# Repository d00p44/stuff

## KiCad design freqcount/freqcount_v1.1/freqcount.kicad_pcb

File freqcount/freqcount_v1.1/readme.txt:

v1.0
  -Cs am Quarz falsch angebunden 
  -kein ISP-Stecker
v1.1
  -Cs am Quarz angepasst
  -ISP-Stecker ergänzt

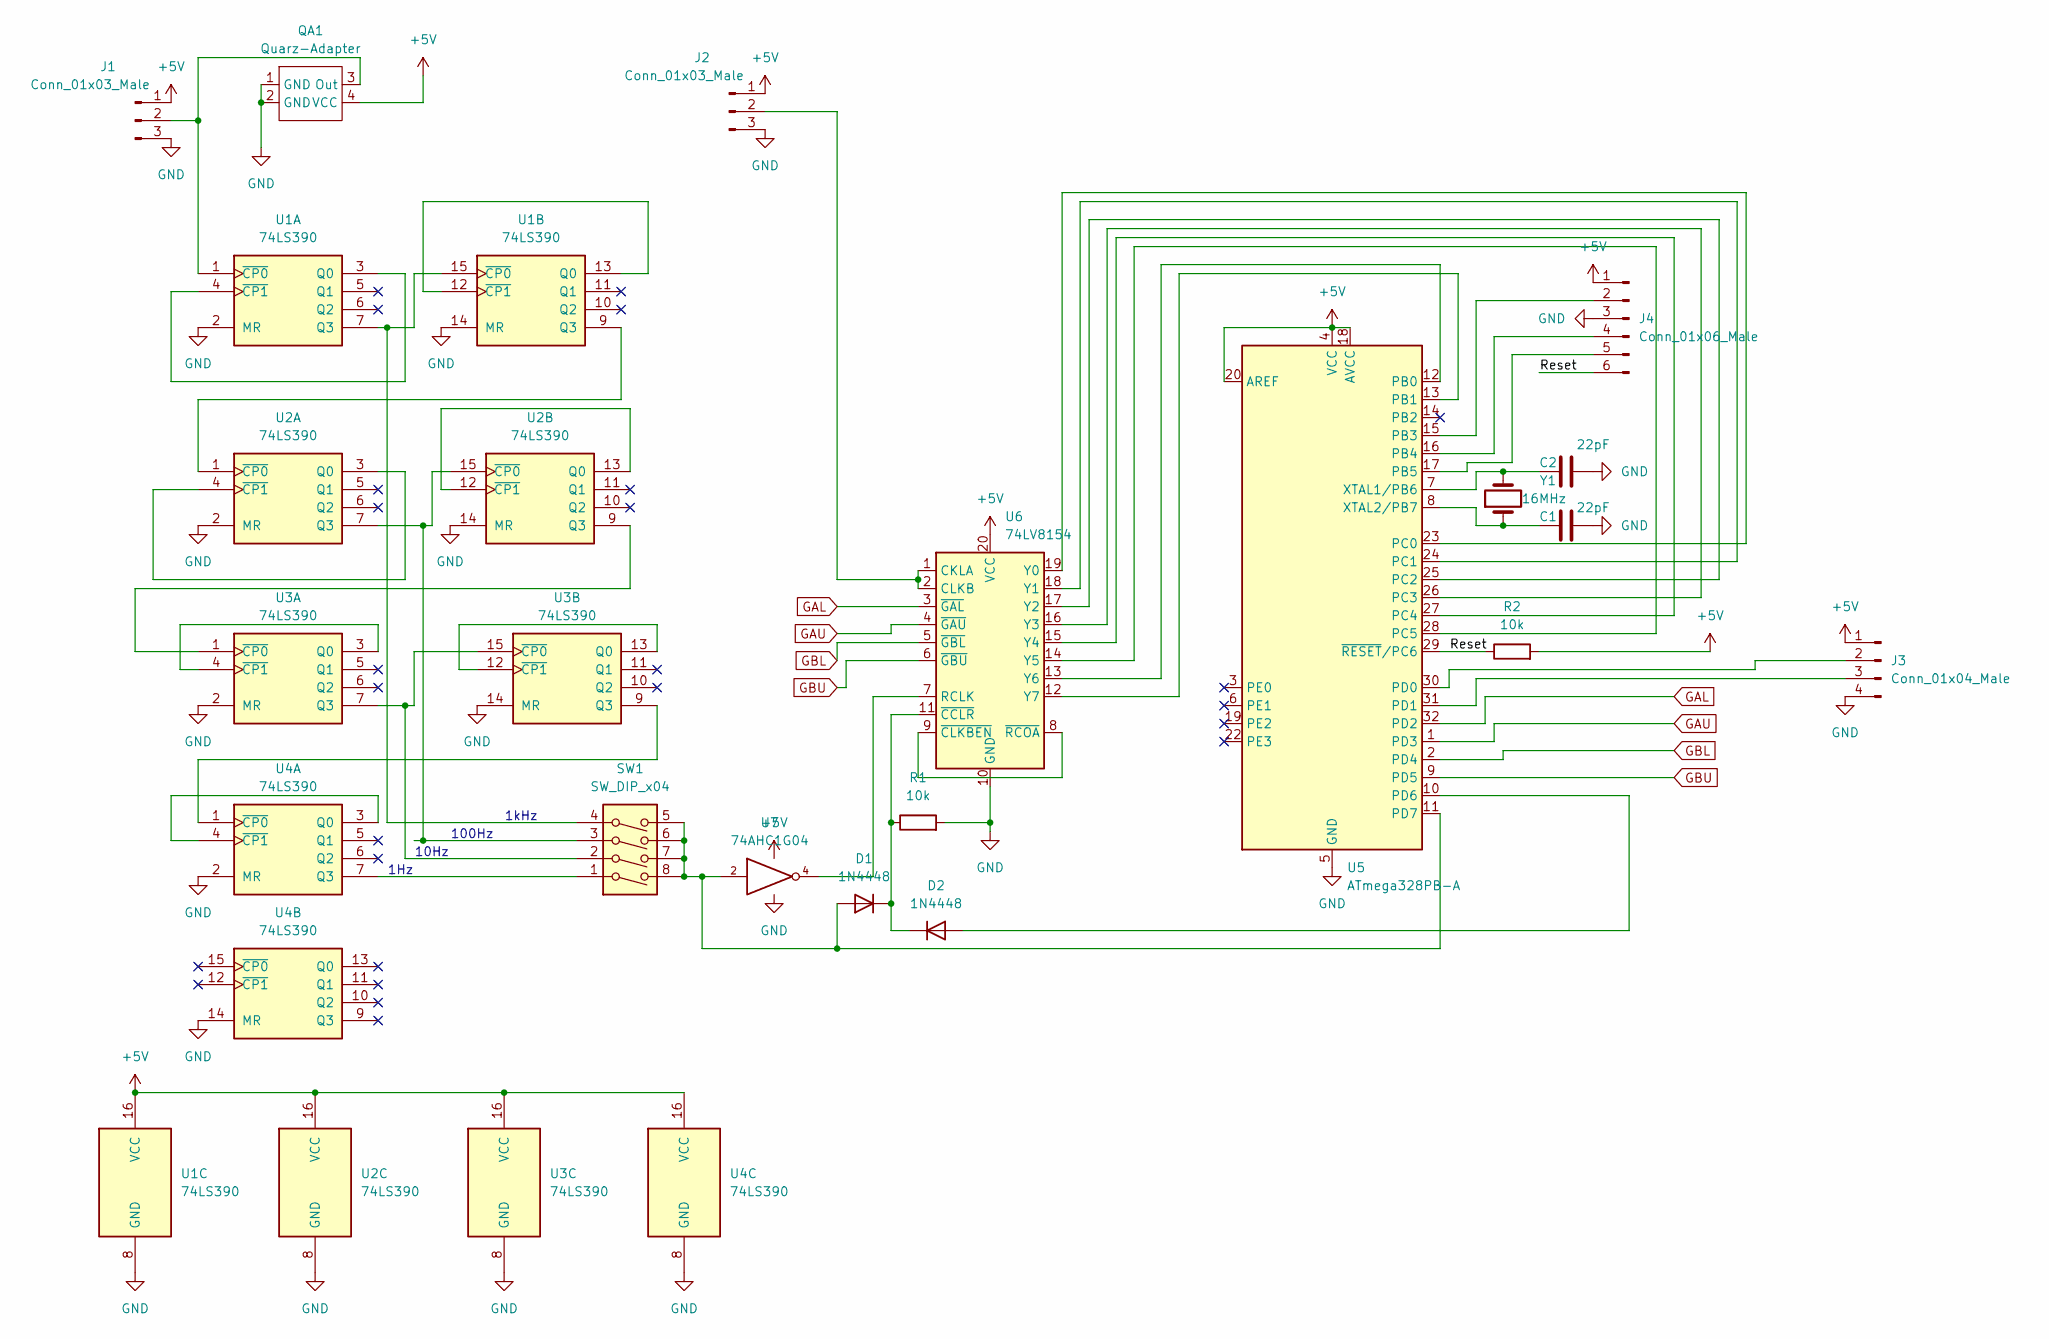
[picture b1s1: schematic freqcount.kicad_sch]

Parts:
C1, C2: 22pF; C_0603_1608Metric
D1, D2: 1N4448; D_SOD-323
J1, J2: Conn_01x03_Male; JST_PH_B3B-PH-K_1x03_P2.00mm_Vertical
J3: Conn_01x04_Male; JST_EH_B4B-EH-A_1x04_P2.50mm_Vertical
J4: Conn_01x06_Male; Molex_PicoBlade_53047-0610_1x06_P1.25mm_Vertical
QA1: Quarz-Adapter
R1, R2: 10k; R_0603_1608Metric
SW1: SW_DIP_x04; SW_DIP_SPSTx04_Slide_KingTek_DSHP04TS_W7.62mm_P1.27mm
U1, U2, U3, U4: 74LS390; SSOP-16_4.4x5.2mm_P0.65mm
U5: ATmega328PB-A; TQFP-32_7x7mm_P0.8mm
U6: 74LV8154; TSSOP-20_4.4x6.5mm_P0.65mm
U7: 74AHC1G04; SOT-23-5
Y1: 16MHz; Crystal_SMD_EuroQuartz_MJ-4Pin_5.0x3.2mm

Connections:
+5V: J1.1, J2.1, J3.1, J4.1, QA1.4 (VCC), R2.2, U1.16 (VCC), U2.16 (VCC), U3.16 (VCC), U4.16 (VCC), U5.4 (VCC), U5.18 (AVCC), U5.20 (AREF), U6.20 (VCC), U7.5 (VCC)
/Reset: J4.6, R2.1, U5.29 (~RESET/PC6)
GAL: U5.32 (PD2), U6.3 (~GAL)
GAU: U5.1 (PD3), U6.4 (~GAU)
GBL: U5.2 (PD4), U6.5 (~GBL)
GBU: U5.9 (PD5), U6.6 (~GBU)
GND: C1.2, C2.2, J1.3, J2.3, J3.4, J4.3, QA1.1 (GND), QA1.2 (GND), R1.2, U1.2 (MR), U1.8 (GND), U1.14 (MR), U2.2 (MR), U2.8 (GND), U2.14 (MR), U3.2 (MR), U3.8 (GND), U3.14 (MR), U4.2 (MR), U4.8 (GND), U4.14 (MR), U5.5 (GND), U5.21 (GND), U6.10 (GND), U7.3 (GND)
unnamed: D1.1 (K), D2.1 (K), R1.1, U6.11 (~CCLR)
unnamed: D1.2 (A), SW1.5, SW1.6, SW1.7, SW1.8, U5.11 (PD7), U7.2
unnamed: D2.2 (A), U5.10 (PD6)
unnamed: J1.2, QA1.3 (Out), U1.1 (~CP0)
unnamed: J2.2, U6.1 (CKLA), U6.2 (CLKB)
unnamed: SW1.1, U4.7 (Q3)
unnamed: SW1.2, U3.7 (Q3), U3.15 (~CP0)
unnamed: SW1.3, U2.7 (Q3), U2.15 (~CP0)
unnamed: SW1.4, U1.7 (Q3), U1.15 (~CP0)
unnamed: U1.3 (Q0), U1.4 (~CP1)
unnamed: U1.9 (Q3), U2.1 (~CP0)
unnamed: U1.12 (~CP1), U1.13 (Q0)
unnamed: U2.3 (Q0), U2.4 (~CP1)
unnamed: U2.9 (Q3), U3.1 (~CP0)
unnamed: U2.12 (~CP1), U2.13 (Q0)
unnamed: U3.3 (Q0), U3.4 (~CP1)
unnamed: U3.9 (Q3), U4.1 (~CP0)
unnamed: U3.12 (~CP1), U3.13 (Q0)
unnamed: U4.3 (Q0), U4.4 (~CP1)
unnamed: C2.1, U5.7 (XTAL1/PB6), Y1.2
unnamed: C1.1, U5.8 (XTAL2/PB7), Y1.1
unnamed: U5.12 (PB0), U6.13 (Y6)
unnamed: U5.13 (PB1), U6.12 (Y7)
unnamed: J4.2, U5.15 (PB3)
unnamed: J4.4, U5.16 (PB4)
unnamed: J4.5, U5.17 (PB5)
unnamed: U5.23 (PC0), U6.19 (Y0)
unnamed: U5.24 (PC1), U6.18 (Y1)
unnamed: U5.25 (PC2), U6.17 (Y2)
unnamed: U5.26 (PC3), U6.16 (Y3)
unnamed: U5.27 (PC4), U6.15 (Y4)
unnamed: U5.28 (PC5), U6.14 (Y5)
unnamed: J3.2, U5.30 (PD0)
unnamed: J3.3, U5.31 (PD1)
unnamed: U6.7 (RCLK), U7.4
unnamed: U6.8 (~RCOA), U6.9 (~CLKBEN)

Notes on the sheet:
1kHz
100Hz
1Hz
10Hz

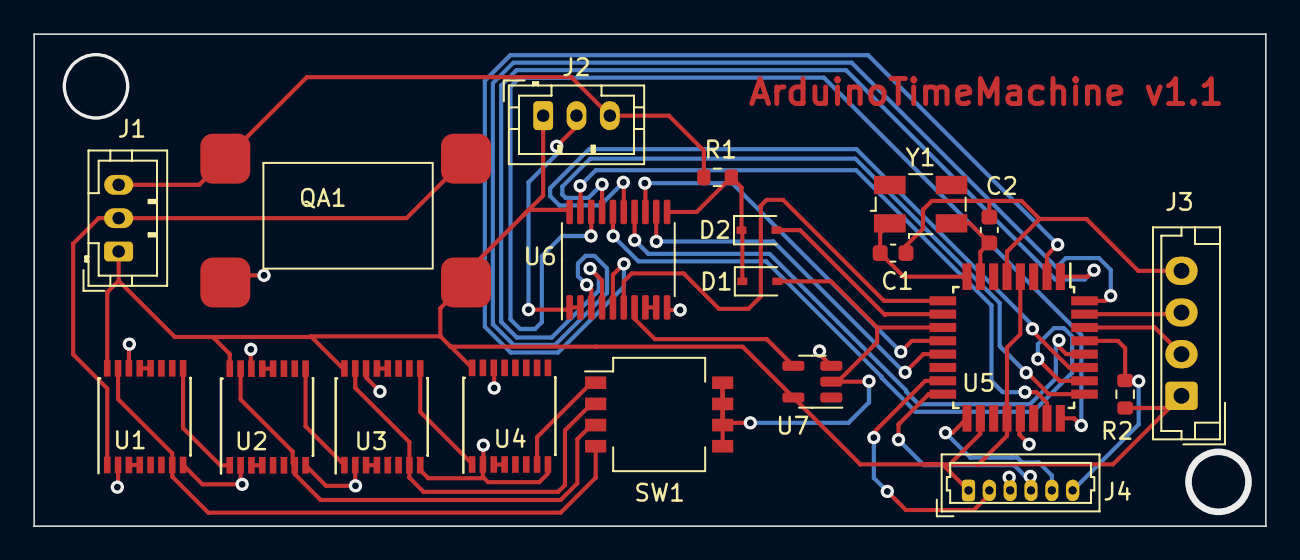
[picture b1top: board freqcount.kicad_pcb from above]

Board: 2 copper layers, 73.9 x 29.5 mm, 20 parts (0 on the bottom side), 43 nets.

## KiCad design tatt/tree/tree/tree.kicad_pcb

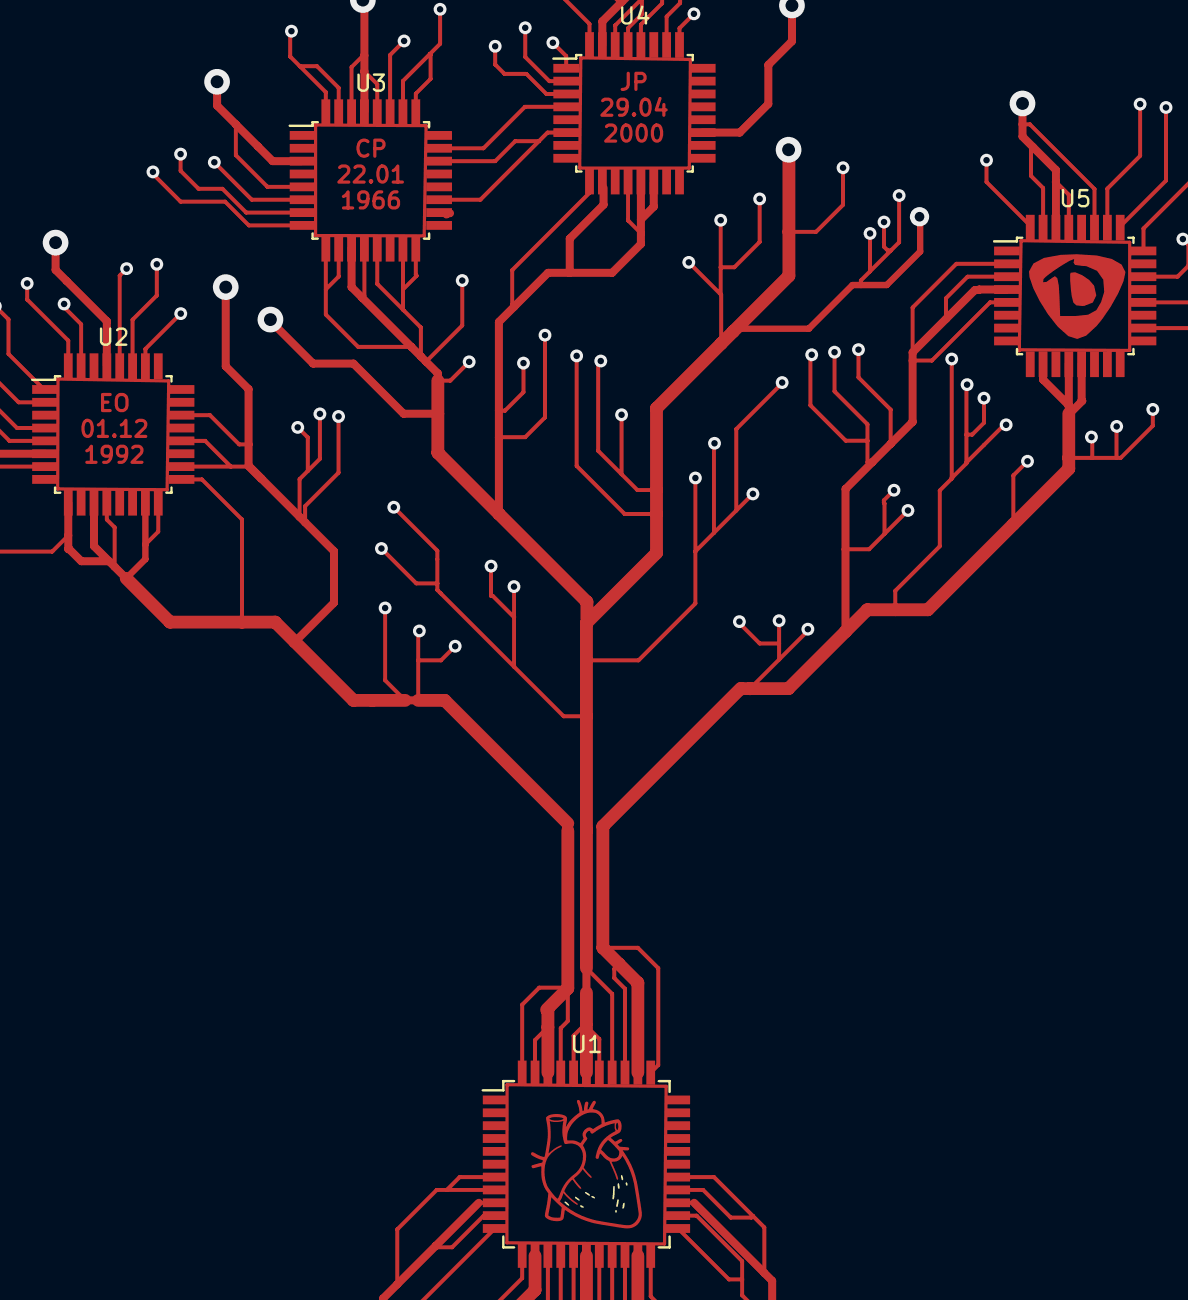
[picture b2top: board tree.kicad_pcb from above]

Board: 2 copper layers, 5 parts (0 on the bottom side), 8 nets.

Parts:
U1: ATmega16L-8A; TQFP-44_10x10mm_P0.8mm
U2, U3, U4, U5: ATmega8-16A; TQFP-32_7x7mm_P0.8mm

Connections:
unnamed: U1.5 (VCC), U5.27 (PC4), U5.29 (PC6/~RESET), U5.30 (PD0), U5.31 (PD1)
unnamed: U1.6 (GND), U1.16 (PD7), U1.17 (VCC), U1.18 (GND), U1.28 (GND)
unnamed: U2.3 (GND), U2.5 (GND)
unnamed: U1.34 (PA3), U1.35 (PA2), U1.36 (PA1), U2.4 (VCC), U2.6 (VCC), U5.2 (PD4), U5.3 (GND), U5.4 (VCC), U5.5 (GND), U5.7 (PB6/XTAL1), U5.10 (PD6), U5.12 (PB0), U5.13 (PB1)
unnamed: U3.3 (GND), U3.5 (GND)
unnamed: U3.4 (VCC), U3.6 (VCC)
unnamed: U4.3 (GND), U4.5 (GND)
unnamed: U4.4 (VCC), U4.6 (VCC)

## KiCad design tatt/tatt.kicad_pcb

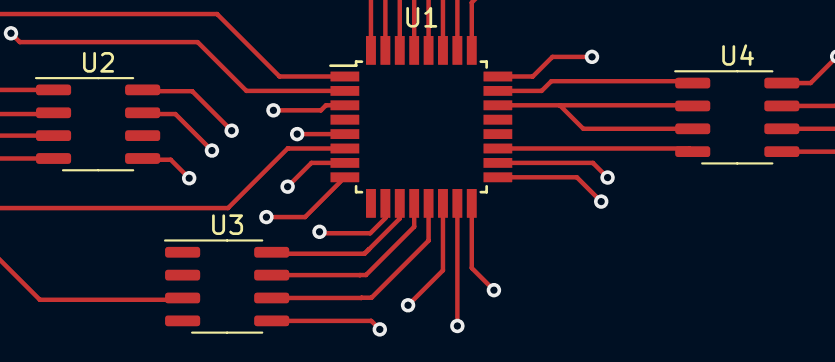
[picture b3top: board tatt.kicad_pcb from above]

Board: 2 copper layers, 4 parts (0 on the bottom side), 13 nets.

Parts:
U1: ATmega8-16A; TQFP-32_7x7mm_P0.8mm
U2, U3, U4: HV9930LG-G; SOIC-8_3.9x4.9mm_P1.27mm

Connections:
GND: U1.3 (GND), U1.5 (GND), U1.20 (AREF), U1.21 (AGND), U1.22 (ADC7), U2.3 (GND), U3.3 (GND), U4.2 (CS1), U4.3 (GND)
unnamed: U1.1 (PD3), U2.1 (VIN)
unnamed: U1.2 (PD4), U2.2 (CS1)
unnamed: U1.7 (PB6/XTAL1), U2.5 (PWMD)
unnamed: U1.8 (PB7/XTAL2), U2.7 (CS2)
unnamed: U1.9 (PD5), U2.8 (REF)
unnamed: U1.10 (PD6), U3.5 (PWMD)
unnamed: U1.4 (VCC), U1.6 (VCC), U1.18 (AVCC), U2.4 (GATE)
unnamed: U1.23 (PC0), U4.1 (VIN)
unnamed: U1.13 (PB1), U3.6 (VDD)
unnamed: U1.12 (PB0), U3.7 (CS2)
unnamed: U1.11 (PD7), U3.8 (REF)
unnamed: U1.19 (ADC6), U4.4 (GATE)

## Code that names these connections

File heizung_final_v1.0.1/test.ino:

#define BUTTON_PIN 8     // PB0
#define LED_PIN 3        // PD3
#define PWM_PIN 5        // PD5
#define TEMP_PIN A1      // PC1
// #define PWM2_PIN 6 // PD6
// #define LED2_PIN 4 // PD4
// #define BUTTON2_PIN 9 // PB1

#define PWM_OFF 0
#define PWM_25 64        // 25% of 255
#define PWM_50 128       // 50% of 255
#define PWM_75 192       // 75% of 255
#define PWM_100 255      // 100% of 255

int pwmLevels[] = {PWM_OFF, PWM_25, PWM_50, PWM_75, PWM_100};
int currentLevel = 0;
unsigned long lastPressTime = 0;
unsigned long buttonPressDuration = 0;
unsigned long lastBlinkTime = 0;
unsigned long lastTempCheckTime = 0;
bool buttonState = LOW;
bool lastButtonState = LOW;

void setup() {
  Serial.begin(9600);
  currentLevel = 0;
  pinMode(BUTTON_PIN, INPUT_PULLUP);
  pinMode(LED_PIN, OUTPUT);
  pinMode(PWM_PIN, OUTPUT);
  analogWrite(PWM_PIN, pwmLevels[currentLevel]);
  }

void loop() {
  unsigned long currentTime = millis();
  
  // Button handling
  buttonState = digitalRead(BUTTON_PIN);
  if (buttonState == LOW && lastButtonState == HIGH) { // Button pressed
    lastPressTime = currentTime;
    buttonPressDuration = 0;
  } else if (buttonState == LOW) { // Button held down
    buttonPressDuration = currentTime - lastPressTime;
  } else if (buttonState == HIGH && lastButtonState == LOW) { // Button released
    if (buttonPressDuration < 2000) {
      currentLevel = (currentLevel + 1);
      if (currentLevel > 4) {currentLevel = 0;}
      analogWrite(PWM_PIN, pwmLevels[currentLevel]);
    } else {
      currentLevel = 0;
      analogWrite(PWM_PIN, pwmLevels[currentLevel]);
    }
  }
  lastButtonState = buttonState;
  
  // LED Blink handling
  if (currentTime - lastBlinkTime >= 5000) {
    lastBlinkTime = currentTime;
    for (int i = 0; i < currentLevel; i++) {
      digitalWrite(LED_PIN, LOW);
      delay(200);
      digitalWrite(LED_PIN, HIGH);
      delay(200);
    }
  }
  
  // Temperature handling
  if (currentTime - lastTempCheckTime >= 5000) {
    lastTempCheckTime = currentTime;
    int sensorValue = analogRead(TEMP_PIN);
    float voltage = sensorValue * (5.0 / 1023.0);
    float resistance = (5.0 - voltage) * 10000 / voltage;
    float temperature = 1.0 / (log(resistance / 10000) / 3435 + 1.0 / 298.15) - 273.15;
    Serial.println(temperature);
    Serial.println(currentLevel);
    if (temperature > 95.0) {
      currentLevel = 0;
      analogWrite(PWM_PIN, pwmLevels[currentLevel]);
    }
  }
}

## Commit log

2021-11-02 Create binaeruhr.cpp
    Binäruhr-Steuerung mit RTC Timekeeper
2021-11-11 code update: fehlerhafte Anzeige von Minute 6 und 7 behoben
2023-05-04 Add files via upload
    added new Roms
2023-05-04 Delete kirbys_dreamland2(USA).h
    not working correctly
2023-05-04 Delete Pokemon_yellow_german.h
    very instable
2024-06-07 Update test.ino
    add pwm2 option
